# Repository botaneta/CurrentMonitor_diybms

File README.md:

Not tested, Modification of the original project https://github.com/pprasse/diyBMS_CurrentVoltage_ADS1115
----------

# diyBMS_CurrentVoltage_ADS1115

Isolated current and isolated voltage sensor for up to 850V & 200A based on ADS1115 and attiny1614 with isolated RS485 / MODBUS. (based on https://github.com/stuartpittaway/diyBMS-CurrentShunt)

# Current / Voltage measurement

The current measurement uses an ACS758ECB-200B hall-effect based current sensor IC.

The voltage measurement is isolated using an ACPL-C870 Precision Optically Isolated Voltage Sensor.

The analog signal from both measurements are converted using a ADS1115 16 bit ADC.

Coulomb calculation takes place in using an attiny1614 and communication uses isolated RS485 / MODBUS.

# Basis

The project is based on https://github.com/stuartpittaway/diyBMS-CurrentShunt and was created to allow using high voltage batteries for diyBMSv4.

# BOARD

The schematics and board are in the directory KiCad.

# CODE / FIRMWARE

The firmware in the directory code is losely based on Stuard Pittaway's diyBMS CurrentShunt. It uses the same MODBUS RTU registers.

## Coulomb calculation

The charge that goes in and out is calculated by sampling the current 128 times per second using the ADS1115 and measuring the time beween each sample. These are then integrated first to mA*ms (uAs) and then every second to mAh (milliamphours).

## Voltage measurement

The voltage is measured every 1 second as it's irrelevant for charge calculation but interesting for power calculation and over/undervoltage checks.

## MODBUS registers

See [MODBUS Registers.md](./code/MODBUS%20Registers.md)

Maximum compatibililty to diyBMS-CurrentShunt should be maintained to allow using the diyBMS4 ESP32 code unmodified.

Please note that due to compatibility the double registers are in mixed endian (floats compromised of 2 16bit registers in little endian, but individual 16 bit registers are big endian) BUT the 32bit integers are big endian.

Use [read-modbus.sh](./code/read-modbus.sh) ```# code/read-modbus.sh``` to read the modbus registers.

# WARNING

This is a DIY product/solution so don’t use this for safety critical systems or in any situation where there could be a risk to life.  

This board was designed to work with high DC voltages which are notoriously dangerous to work with and are a risk to life. Please make sure you have the appropriate knowledge and always use fuses specified for DC.

There is no warranty, it may not work as expected or at all.

The use of this project is done so entirely at your own risk.  It may involve electrical voltages which could kill - if in doubt, seek help.

The use of this project may not be compliant with local laws or regulations - if in doubt, seek help.

# License

This work is licensed under a Creative Commons Attribution-NonCommercial-ShareAlike 2.0 UK: England & Wales License.

https://creativecommons.org/licenses/by-nc-sa/2.0/uk/

You are free to:
* Share — copy and redistribute the material in any medium or format
* Adapt — remix, transform, and build upon the material
The licensor cannot revoke these freedoms as long as you follow the license terms.

Under the following terms:
* Attribution — You must give appropriate credit, provide a link to the license, and indicate if changes were made. You may do so in any reasonable manner, but not in any way that suggests the licensor endorses you or your use.
* Non-Commercial — You may not use the material for commercial purposes.
* ShareAlike — If you remix, transform, or build upon the material, you must distribute your contributions under the same license as the original.
* No additional restrictions — You may not apply legal terms or technological measures that legally restrict others from doing anything the license permits.

Notices:
You do not have to comply with the license for elements of the material in the public domain or where your use is permitted by an applicable exception or limitation.

No warranties are given. The license may not give you all of the permissions necessary for your intended use. For example, other rights such as publicity, privacy, or moral rights may limit how you use the material.

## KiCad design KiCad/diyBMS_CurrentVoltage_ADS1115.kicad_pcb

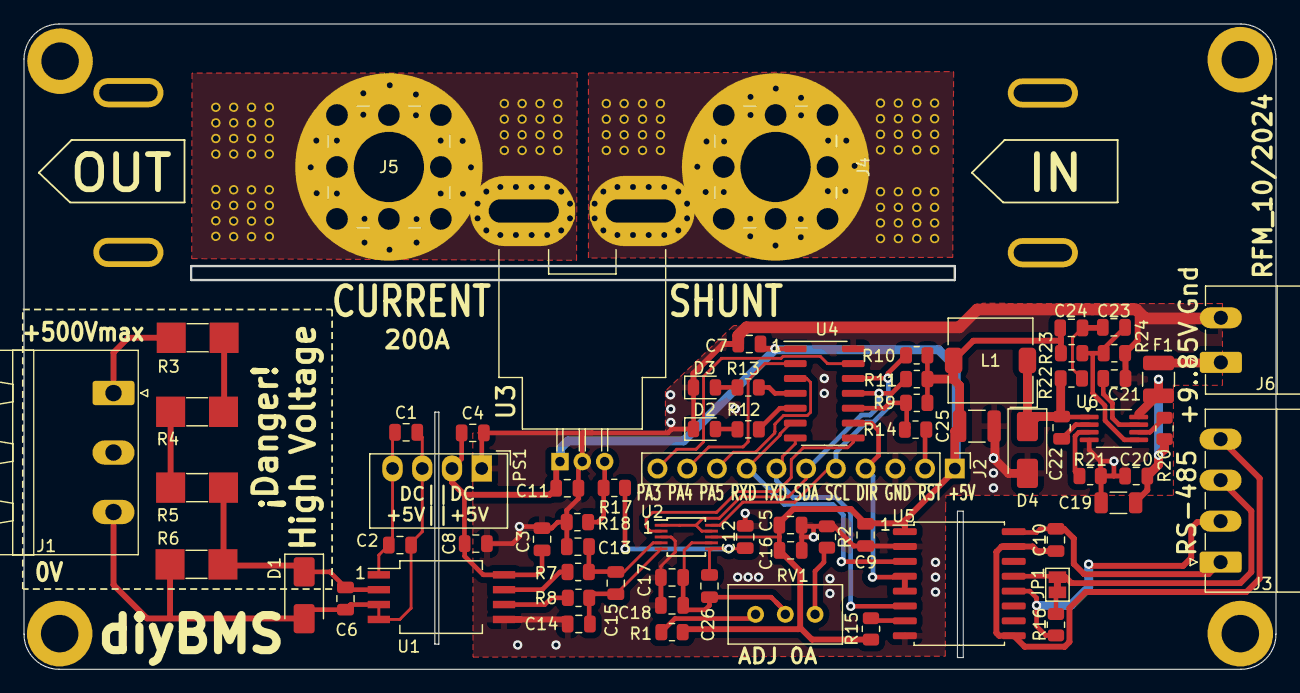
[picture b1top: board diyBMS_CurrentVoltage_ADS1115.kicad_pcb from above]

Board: 2 copper layers, 106.8 x 55.0 mm, 70 parts (0 on the bottom side), 49 nets.

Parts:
C1, C4, C7, C16, C18: 10u; C_0805_2012Metric
C2, C3, C5, C11, C12, C13, C14, C15, C17, C26: 100n; C_0805_2012Metric
C6: 1n; C_0805_2012Metric
C8, C9, C10: 100nF; C_0805_2012Metric
C19: 1uF; C_1206_3216Metric
C20: 100nF 100V; C_0805_2012Metric
C21: 1uF; C_0805_2012Metric
C22, C23: 10nF; C_0805_2012Metric
C24: 3.3nF; C_0805_2012Metric
C25: 47uF; C_1210_3225Metric
D1: SMAJ5.0A; D_SMA
D2: GREEN; LED_0805_2012Metric
D3: RED; LED_0805_2012Metric
D4: 400V 1A 1.3V @ 1A 150ns SMA; D_SMA
F1: Fuse, 0.5A; Fuse_1210_3225Metric
J1: Screw_Terminal_01x03; PhoenixContact_MSTBA_2,5_3-G-5,08_1x03_P5.08mm_Horizontal
J2: Conn_01x11_Pin; PinHeader_1x11_P2.54mm_Vertical
J3: Screw_Terminal_01x04; PhoenixContact_MC_1,5_4-G-3.5_1x04_P3.50mm_Horizontal
J4, J5: 9x9 PIN connector; Wuerth_REDCUBE-THR_WP-THRBU_74650194_THR
J6: Screw_Terminal_01x02; PhoenixContact_MC_1,5_2-G-3.81_1x02_P3.81mm_Horizontal
JP1: SolderJumper_2_Bridged; SolderJumper-2_P1.3mm_Bridged_Pad1.0x1.5mm
L1: 1mH; L_TDK_SLF7045
PS1: MEE1S0505SC; Converter_DCDC_Murata_MEE1SxxxxSC_THT
R1, R2, R10, R11, R18: 4k7; R_0805_2012Metric
R3, R4, R5: 402k; PP | R_MELF_MMB-0207 | 0805 Compatible
R6: 4k7; PP _ R_MELF_MMB-0207 _ 0805 Compatible
R7, R8, R17, R23, R24: 10k; R_0805_2012Metric
R9: 100K; R_0805_2012Metric
R12, R13: 330R; R_0805_2012Metric
R14: 470R; R_0805_2012Metric
R15: 10K; R_0805_2012Metric
R16: 120R; R_0805_2012Metric
R20: 680k; R_0805_2012Metric
R21: 150k; R_0805_2012Metric
R22: 470k; R_0805_2012Metric
RV1: 500R; Potentiometer_Bourns_3296W_Vertical
U1: ACPL-C870; SSO-8_6.8x5.9mm_P1.27mm_Clearance8mm
U2: ADS1115IDGS; TSSOP-10_3x3mm_P0.5mm
U3: ACS758xCB-200B-PFF; Allegro_CB_PFF
U4: ATtiny1614-SS; SOIC-14_3.9x8.7mm_P1.27mm
U5: ADM2483xRW; SOIC-16W_7.5x10.3mm_P1.27mm
U6: LM5009A; MSOP-8_3x3mm_P0.65mm

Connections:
+5V: C3.1, C4.1, C5.1, C7.1, C8.1, C9.1, C11.1, C16.2, C24.1, C25.2, J2.1, L1.2, PS1.2 (+Vin), R1.2, R9.2, R10.1, R11.1, R15.1, R23.1, U1.8 (VDD2), U2.8 (VDD), U3.1 (VCC), U4.1 (VCC), U5.1 (VDD1)
+5VP: C1.1, C2.1, PS1.4 (+Vout), U1.1 (VDD1)
A: J3.2, R16.2, U5.12 (A)
ALERT: U2.2 (ALERT/RDY), U4.8 (PB1)
B: J3.3, JP1.2 (B), U5.13 (B)
GND: C3.2, C4.2, C5.2, C7.2, C8.2, C9.2, C11.2, C12.2, C13.1, C14.2, C16.1, C17.2, C18.2, C19.2, C20.2, C21.1, C25.1, D2.1 (K), D3.1 (K), D4.2 (A), J2.3, J6.2, PS1.1 (-Vin), R2.2, R18.2, R21.2, R24.2, U1.5 (GND2), U2.3 (GND), U3.2 (GND), U4.14 (GND), U5.2 (GND1), U5.8 (GND1), U6.4 (RTN)
GND1: C1.2, C2.2, C6.2, D1.2 (A2), J1.3, PS1.3 (-Vout), R6.2, U1.3 (IN-), U1.4 (GND1)
GND2: C10.1, J3.4, U5.9 (GND2), U5.15 (GND2)
unnamed: C23.2, C24.2, R22.2
unnamed: C6.1, D1.1 (A1), R5.2, R6.1, U1.2 (IN)
unnamed: D2.2 (A), R12.1
unnamed: D3.2 (A), R13.1
unnamed: C22.2, D4.1 (K), L1.1, R22.1, U6.1 (SW)
unnamed: J1.1, R3.1
unnamed: J2.2, R14.1
unnamed: J4.1, U3.4 (IP+)
unnamed: J5.1, U3.5 (IP-)
unnamed: F1.2, J6.1
unnamed: JP1.1 (A), R16.1
unnamed: R1.1, RV1.1
unnamed: R2.1, RV1.3
unnamed: R3.2, R4.1
unnamed: R4.2, R5.1
unnamed: R7.1, U1.7 (OUT+)
unnamed: R8.1, U1.6 (OUT-)
unnamed: C13.2, C15.2, R7.2, U2.4 (AIN0)
unnamed: C14.1, C15.1, R8.2, U2.5 (AIN1)
unnamed: C12.1, C26.2, R17.1, U2.6 (AIN2)
unnamed: C17.1, C18.1, C26.1, RV1.2, U2.7 (AIN3)
unnamed: R17.2, R18.1, U3.3 (VIOUT)
unnamed: R15.2, U5.7 (PV)
unnamed: C22.1, U6.2 (BST)
unnamed: C23.1, R23.2, R24.1, U6.5 (FB)
unnamed: R21.1, U6.3 (RCL)
unnamed: R20.2, U6.6 (Rt/SD)
unnamed: C21.2, U6.7 (VCC)
unnamed: C19.1, C20.1, F1.1, R20.1, U6.8 (VIN)
PA3: J2.11, U4.13 (PA3)
PA4: J2.10, U4.2 (PA4)
PA5: J2.9, U4.3 (PA5)
PA6: R13.2, U4.4 (PA6)
PA7: R12.2, U4.5 (PA7)
RESET: R9.1, R14.2, U4.10 (~RESET/PA0)
RXD: J2.8, U4.6 (PB3), U5.3 (RxD)
SCL: J2.5, R10.2, U2.10 (SCL), U4.12 (PA2)
SDA: J2.6, R11.2, U2.1 (ADDR), U2.9 (SDA), U4.11 (PA1)
TXD: J2.7, U4.7 (PB2), U5.6 (TxD)
VDD2: C10.2, J3.1, U5.16 (VDD2)
XDIR: J2.4, U4.9 (PB0), U5.4 (~RE), U5.5 (DE)

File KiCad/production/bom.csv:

Designator,Footprint,Quantity,Value,LCSC Part #
"_143, _142, _141, _140, _139, _138, _137, _136, _135, _134, _133, _132, _131, _130, _129, _128, _127, _126, _125, _124, _123, _122, _121, _120, _119, _118, _117, _116, _115, _114, _113, _112, _111, _110, _109, _108, _107, _106, _105, _104, _103, _102, _101, _100, _99, _98, _97, _96, _95, _94, _93, _92, _91, _90, _89, _88, _87, _86, _85, _84, _83, _82, _81, _80, _79, _78, _77, _76, _75, _74, _73, _72, _71, _70, _69, _68, _67, _66, _65, _64, _63, _62, _61, _60, _59, _58, _57, _56, _55, _54, _53, _52, _51, _50, _49, _48, _47, _46, _45, _44, _43, _42, _41, _40, _39, _38, _37, _36, _35, _34, _33, _32, _31, _30, _29, _28, _27, _26, _25, _24, _23, _22, _21, _20, _19, _18, _17, _16, _15, _14, _13, _12, _11, _10, _9, _8, _7, _6, _5, _4, _3, _2, ",,143,,
"C1, C16, C18, C4, C7",0805,5,10u,
"C10, C8, C9",0805,3,100nF,
"C11, C12, C13, C14, C15, C17, C2, C26, C3, C5",0805,10,100n,
C19,1206,1,1uF,
C20,0805,1,100nF 100V,
C21,0805,1,1uF,
"C22, C23",0805,2,10nF,
C24,0805,1,3.3nF,
C25,1210,1,47uF,
C6,0805,1,1n,
D1,D_SMA,1,SMAJ5.0A,
D2,0805,1,GREEN,
D3,0805,1,RED,
D4,D_SMA,1,400V 1A 1.3V @ 1A 150ns SMA,
F1,1210,1,"Fuse, 0.5A",
J1,"PhoenixContact_MSTBA_2,5_3-G-5,08_1x03_P5.08mm_Horizontal",1,Screw_Terminal_01x03,
J2,PinHeader_1x11_P2.54mm_Vertical,1,Conn_01x11_Pin,
J3,"PhoenixContact_MC_1,5_4-G-3.5_1x04_P3.50mm_Horizontal",1,Screw_Terminal_01x04,
J4,Wuerth_REDCUBE-THR_WP-THRBU_74650194_THR,1,9x9 PIN connector,
J6,"PhoenixContact_MC_1,5_2-G-3.81_1x02_P3.81mm_Horizontal",1,Screw_Terminal_01x02,
JP1,SolderJumper-2_P1.3mm_Bridged_Pad1.0x1.5mm,1,SolderJumper_2_Bridged,
L1,L_TDK_SLF7045,1,1mH,
PS1,Converter_DCDC_Murata_MEE1SxxxxSC_THT,1,MEE1S0505SC,
"R1, R10, R11, R18, R2",0805,5,4k7,
"R12, R13",0805,2,330R,
R14,0805,1,470R,
"R15, R17, R23, R24, R7, R8",0805,6,10K,
R16,0805,1,120R,
R20,0805,1,680k,
R21,0805,1,150k,
R22,0805,1,470k,
"R3, R4, R5",PP | R_MELF_MMB-0207 | 0805 Compatible,3,402k,
R6,PP _ R_MELF_MMB-0207 _ 0805 Compatible,1,4k7,
R9,0805,1,100K,
RV1,Potentiometer_Bourns_3296W_Vertical,1,500,
U1,SSO-8_6.8x5.9mm_P1.27mm_Clearance8mm,1,ACPL-C870,
U2,TSSOP-10_3x3mm_P0.5mm,1,ADS1115IDGS,
U3,Allegro_CB_PFF,1,ACS758xCB-200B-PFF,
U4,SOIC-14_3.9x8.7mm_P1.27mm,1,ATtiny1614-SS,
U5,SOIC-16W_7.5x10.3mm_P1.27mm,1,ADM2483xRW,
U6,MSOP-8_3x3mm_P0.65mm,1,LM5009A,

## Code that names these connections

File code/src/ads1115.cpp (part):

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

    Wire.begin();
    // Change TWI pins to use PA1/PA2 and not PB1/PB0
    Wire.swap(1);
    // Use fast i2c
    Wire.setClock(400000);
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

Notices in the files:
code/src/ads1115.cpp:
(c)2023 Patrick Prasse
Attribution-NonCommercial-ShareAlike 2.0 UK: England & Wales (CC BY-NC-SA 2.0 UK)
